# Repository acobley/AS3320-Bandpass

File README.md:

View this project on [CADLAB.io](https://cadlab.io/project/24867). 

# AS3320-Bandpass
This is a bandpass filter with CV control of the resonce based on a single  AS3320

Status: In Design

Board: No Board sent to manfacturer.

## Licence and attribution
CC4.0

Based on the work by forestcaver/Analog-Voice (github)

## Major aditions
* Added CV on Resonance
* Moved to larger components (0804)
* Added more inputs and input mixer out.

## History
as3320-BandPass-Dev2 10/Nov/2021 This board is untested. D6 repositioned.

as3320-BandPass-Dev1  2/oct/2021 D6 is shorted to FM level POT Do NOT USE (To use, a TTH D6 can be substituted  betweenthe output pin and ground.

10/Nov/2021 Rec2021 Recieved and will be built with above botch. 

as3320-BandPass Layout version

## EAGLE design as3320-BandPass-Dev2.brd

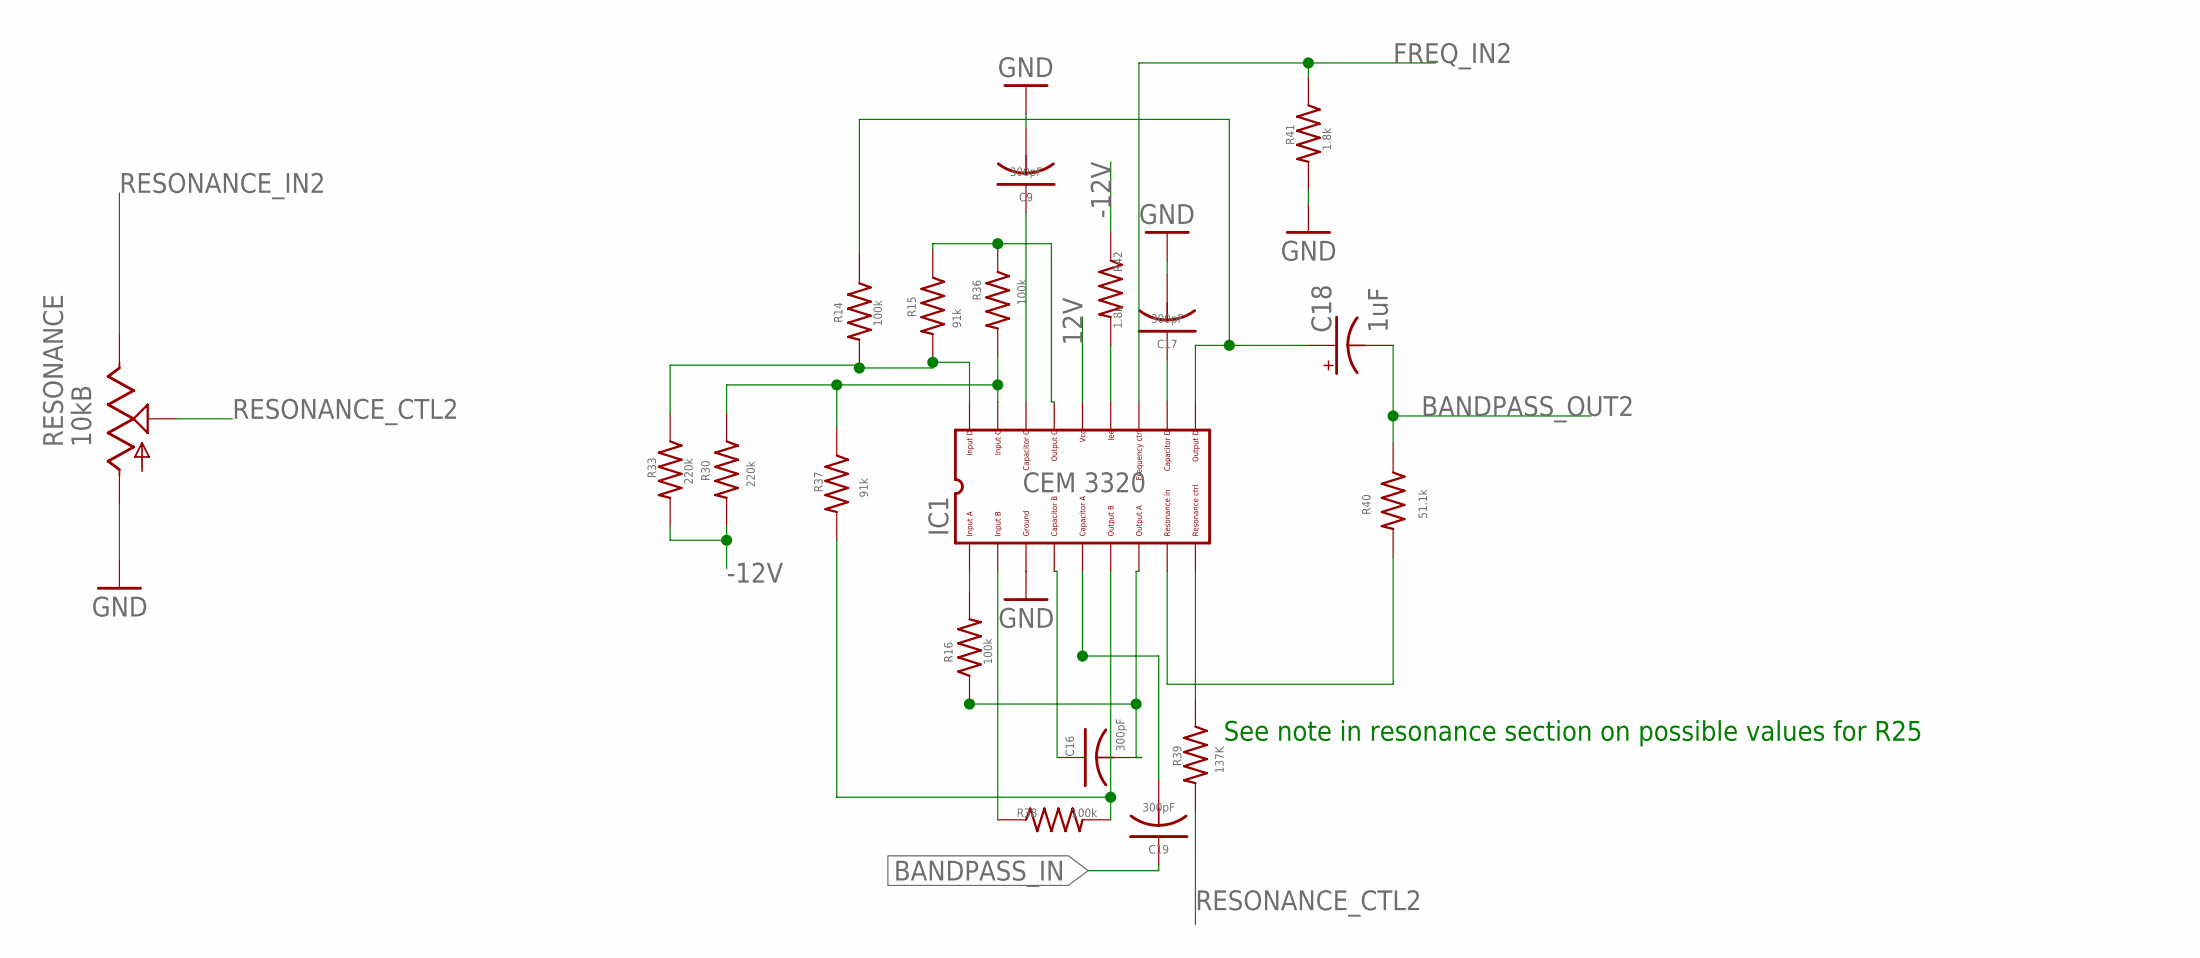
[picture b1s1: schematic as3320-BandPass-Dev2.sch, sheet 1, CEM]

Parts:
C9, C16, C17, C19: 300pF; C0805K
C18: 1uF; PANASONIC_B
IC1: CEM3320; DIL18
R14, R16, R36, R38: 100k; GMSN_M0805
R15, R37: 91k; GMSN_M0805
R30, R33: 220k; GMSN_M0805
R39: 137K; GMSN_M0805
R40: 51.1k; GMSN_M0805
R41, R42: 1.8k; GMSN_M0805
RESONANCE: 10kB; ALPS_POT_VERTICAL

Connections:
12V: IC1.14; also elsewhere on the board
-12V: R30.2, R33.2, R42.1; also elsewhere on the board
BANDPASS_IN: C19.1; also elsewhere on the board
BANDPASS_OUT2: C18.-, R40.1; also elsewhere on the board
FREQ_IN2: IC1.12, R41.1; also elsewhere on the board
GND: C9.2, C17.2, IC1.3, R41.2, RESONANCE.P$3 (A); also elsewhere on the board
unnamed: C17.1, IC1.11
unnamed: IC1.9, R39.1
unnamed: IC1.8, R40.2
unnamed: IC1.13, R42.2
unnamed: C9.1, IC1.16
unnamed: C18.+, IC1.10, R14.1
unnamed: C19.2, IC1.5
unnamed: C16.2, IC1.7, R16.1
unnamed: C16.1, IC1.4
unnamed: IC1.2, R38.1
unnamed: IC1.6, R37.2, R38.2
unnamed: IC1.1, R16.2
unnamed: IC1.17, R30.1, R36.2, R37.1
unnamed: IC1.15, R15.1, R36.1
unnamed: IC1.18, R14.2, R15.2, R33.1
RESONANCE_CTL2: R39.2, RESONANCE.P$2 (S)
RESONANCE_IN2: RESONANCE.P$1 (E); also elsewhere on the board

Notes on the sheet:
See note in resonance section on possible values for R25

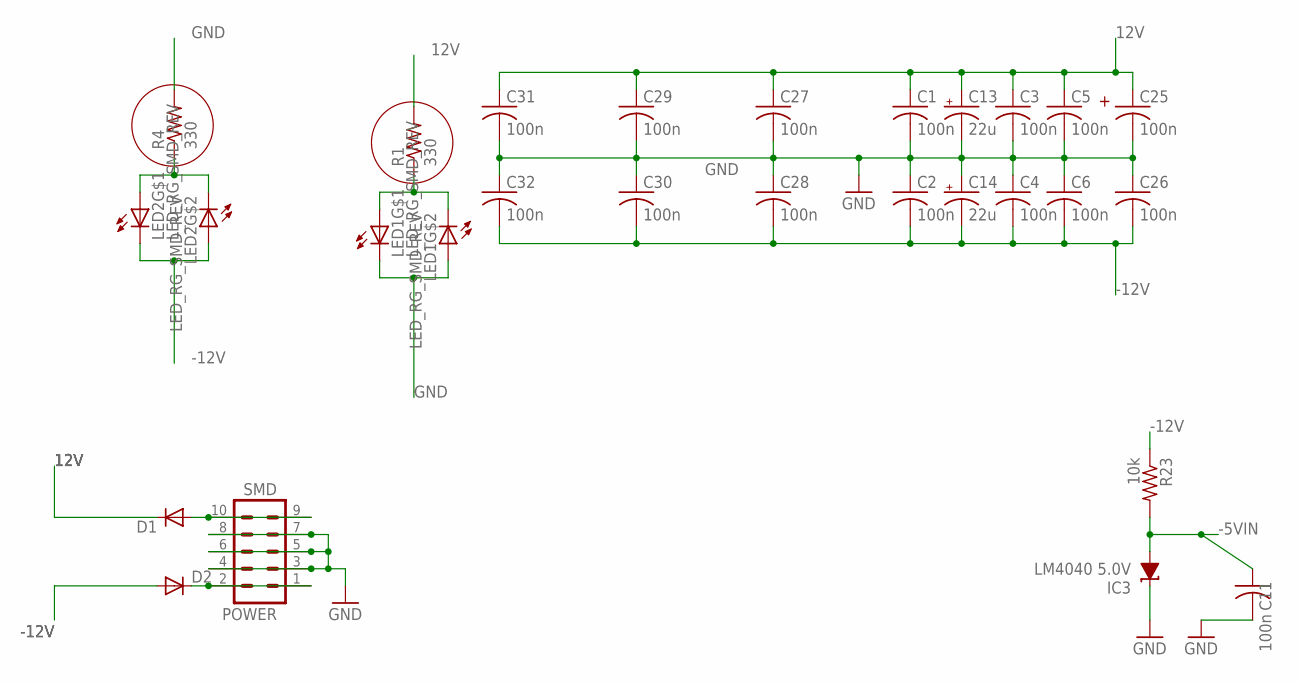
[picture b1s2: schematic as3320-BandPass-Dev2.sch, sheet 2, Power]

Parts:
C1, C2, C3, C4, C5, C6, C25, C26, C27, C28, C29, C30, C31, C32: 100n; C0805K
C11: 100n; GMSN_C0805K
C13, C14: 22u; PANASONIC_B
D1, D2: 1N5819HW; SOD123
IC3: LM4040 5.0V; DBZ_R-PDSO-G3
LED1, LED2: LED_RG_SMD_REV; LSG_T77K
POWER: SMD; 2X5-SHROUDED_SMD
R1, R4: 330; GMSN_M0805
R23: 10k; GMSN_M0805

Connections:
12V: C1.1, C3.1, C5.1, C13.+, C25.1, C27.1, C29.1, C31.1, D1.C, R1.2; also elsewhere on the board
-5VIN: C11.1, IC3.2 (A), R23.2; also elsewhere on the board
-12V: C2.2, C4.2, C6.2, C14.-, C26.2, C28.2, C30.2, C32.2, D2.A, LED2.1 (C), LED2.4 (A), R23.1; also elsewhere on the board
-12V-P: D2.C, POWER.1, POWER.2
GND: C1.2, C2.1, C3.2, C4.1, C5.2, C6.1, C11.2, C13.-, C14.+, C25.2, C26.1, C27.2, C28.1, C29.2, C30.1, C31.2, C32.1, IC3.1 (C), LED1.1 (C), LED1.4 (A), POWER.3, POWER.4, POWER.5, POWER.6, POWER.7, POWER.8, R4.2; also elsewhere on the board
unnamed: D1.A, POWER.9, POWER.10
unnamed: LED2.2 (A), LED2.3 (C), R4.1
unnamed: LED1.2 (A), LED1.3 (C), R1.1

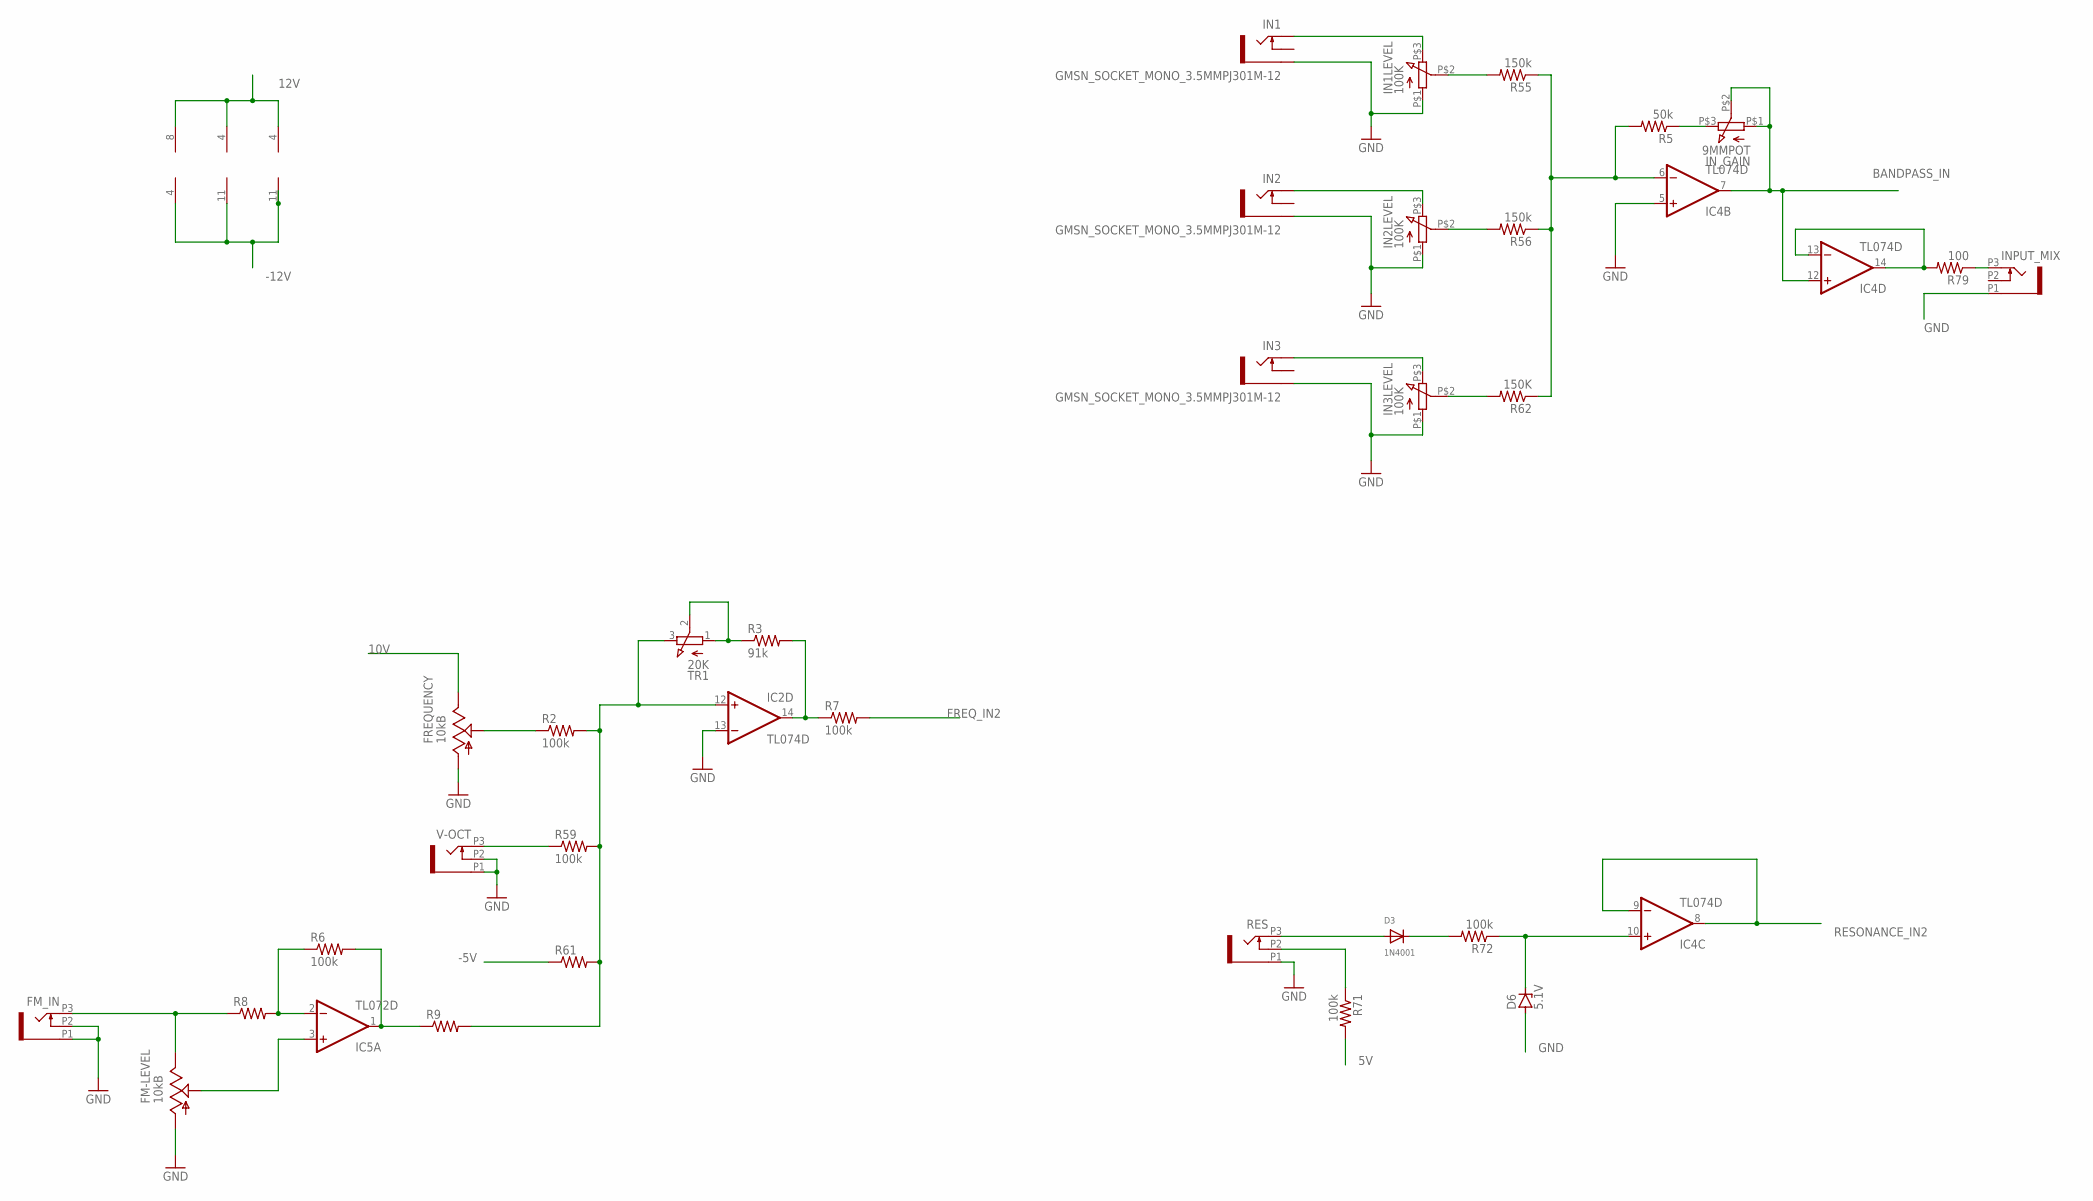
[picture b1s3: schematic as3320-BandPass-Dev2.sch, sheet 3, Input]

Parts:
D3: 1N4001; SMADIODE
D6: 5.1V; SOT23
FM-LEVEL: 10kB; ALPS_POT_VERTICAL
FM_IN: PJ301_THONKICONN6; WQP_PJ_301M6
FREQUENCY: 10kB; ALPS_POT_VERTICAL
IC2, IC4: TL074D; SO14
IC5: TL072D; SO08
IN1, IN2, IN3: GMSN_SOCKET_MONO_3.5MMPJ301M-12; GMSN_PJ301M-12
IN1LEVEL, IN2LEVEL, IN3LEVEL: 100K; POT
INPUT_MIX: PJ301_THONKICONN6; WQP_PJ_301M6
IN_GAIN: 9MMPOT; POT
R2, R6, R7, R59, R72: 100k; GMSN_M0805
R3: 91k; GMSN_M0805
R5: 50k; GMSN_M0805
R8, R9, R61: 62k; GMSN_M0805
R55, R56: 150k; R0805
R62: 150K; R0805
R71: 100k; R0805
R79: 100; GMSN_M0805
RES: PJ301_THONKICONN6; WQP_PJ_301M6
TR1: 20K; TRIMMER_TH3
V-OCT: PJ301_THONKICONN6; WQP_PJ_301M6

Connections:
5V: R71.2; also elsewhere on the board
10V: FREQUENCY.P$1 (E); also elsewhere on the board
12V: IC2.4 (V+), IC4.4 (V+), IC5.8 (V+); also elsewhere on the board
-5V: R61.1; also elsewhere on the board
-12V: IC2.11 (V-), IC4.11 (V-), IC5.4 (V-); also elsewhere on the board
BANDPASS_IN: IC4.7 (OUT), IC4.12 (+IN), IN_GAIN.P$1 (1), IN_GAIN.P$2 (2); also elsewhere on the board
FREQ_IN2: R7.2; also elsewhere on the board
GND: D6.1 (A), FM-LEVEL.P$3 (A), FM_IN.P1 (1), FM_IN.P2 (2), FREQUENCY.P$3 (A), IC2.13 (-IN), IC4.5 (+IN), IN1.GND (SLEEVE), IN1LEVEL.P$1 (1), IN2.GND (SLEEVE), IN2LEVEL.P$1 (1), IN3.GND (SLEEVE), IN3LEVEL.P$1 (1), INPUT_MIX.P1 (1), RES.P1 (1), V-OCT.P1 (1), V-OCT.P2 (2); also elsewhere on the board
unnamed: IC5.2 (-IN), R6.1, R8.2
unnamed: IC2.14 (OUT), R3.2, R7.1
unnamed: IC5.1 (OUT), R6.2, R9.1
unnamed: FREQUENCY.P$2 (S), R2.1
unnamed: FM-LEVEL.P$2 (S), IC5.3 (+IN)
unnamed: FM-LEVEL.P$1 (E), FM_IN.P3 (3), R8.1
unnamed: R71.1, RES.P2 (2)
unnamed: IC2.12 (+IN), R2.2, R9.2, R59.2, R61.2, TR1.3
unnamed: IN_GAIN.P$3 (3), R5.1
unnamed: R59.1, V-OCT.P3 (3)
unnamed: R3.1, TR1.1, TR1.2
unnamed: IN1.TIP, IN1LEVEL.P$3 (3)
unnamed: IN2.TIP, IN2LEVEL.P$3 (3)
unnamed: D3.A, RES.P3 (3)
unnamed: IN1LEVEL.P$2 (2), R55.2
unnamed: IN2LEVEL.P$2 (2), R56.2
unnamed: IN3.TIP, IN3LEVEL.P$3 (3)
unnamed: IN3LEVEL.P$2 (2), R62.2
unnamed: IC4.6 (-IN), R5.2, R55.1, R56.1, R62.1
unnamed: D3.C, R72.2
unnamed: D6.3 (C), IC4.10 (+IN), R72.1
unnamed: IC4.13 (-IN), IC4.14 (OUT), R79.2
unnamed: INPUT_MIX.P3 (3), R79.1
RESONANCE_IN2: IC4.8 (OUT), IC4.9 (-IN); also elsewhere on the board

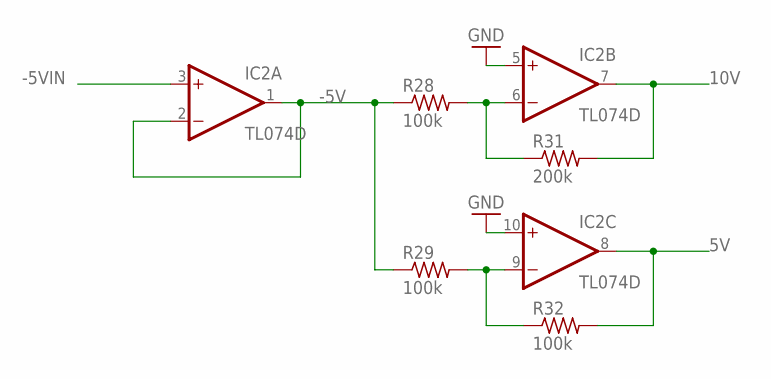
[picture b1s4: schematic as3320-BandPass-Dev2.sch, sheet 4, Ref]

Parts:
IC2: TL074D; SO14
R28, R29, R32: 100k; GMSN_M0805
R31: 200k; GMSN_M0805

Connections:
5V: IC2.8 (OUT), R32.2; also elsewhere on the board
10V: IC2.7 (OUT), R31.2; also elsewhere on the board
-5V: IC2.1 (OUT), IC2.2 (-IN), R28.1, R29.1; also elsewhere on the board
-5VIN: IC2.3 (+IN); also elsewhere on the board
GND: IC2.5 (+IN), IC2.10 (+IN); also elsewhere on the board
unnamed: IC2.9 (-IN), R29.2, R32.1
unnamed: IC2.6 (-IN), R28.2, R31.1

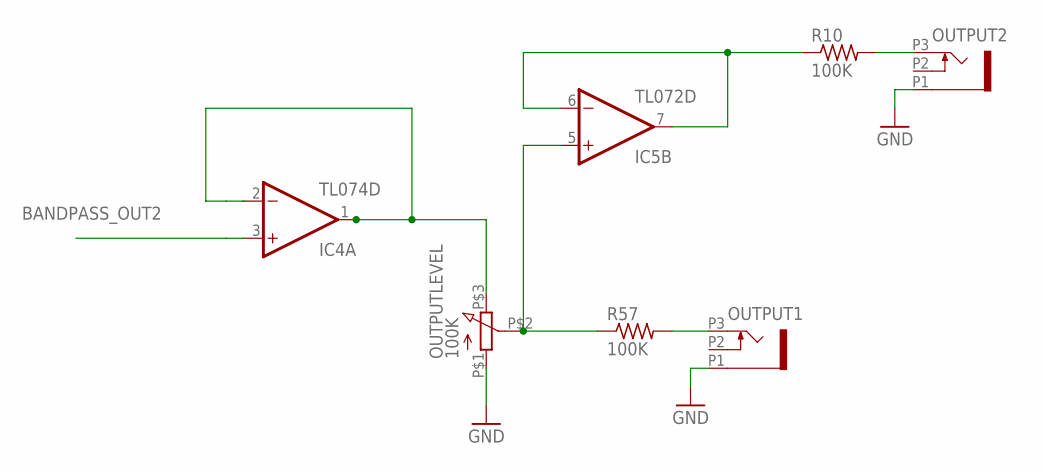
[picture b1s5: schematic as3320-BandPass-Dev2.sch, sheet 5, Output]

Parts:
IC4: TL074D; SO14
IC5: TL072D; SO08
OUTPUT1, OUTPUT2: PJ301_THONKICONN6; WQP_PJ_301M6
OUTPUTLEVEL: 100K; POT
R10, R57: 100K; GMSN_M0805

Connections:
BANDPASS_OUT2: IC4.3 (+IN); also elsewhere on the board
GND: OUTPUT1.P1 (1), OUTPUT2.P1 (1), OUTPUTLEVEL.P$1 (1); also elsewhere on the board
unnamed: IC5.5 (+IN), OUTPUTLEVEL.P$2 (2), R57.1
unnamed: IC5.6 (-IN), IC5.7 (OUT), R10.1
unnamed: IC4.1 (OUT), IC4.2 (-IN), OUTPUTLEVEL.P$3 (3)
O1: OUTPUT2.P3 (3), R10.2
O2: OUTPUT1.P3 (3), R57.2

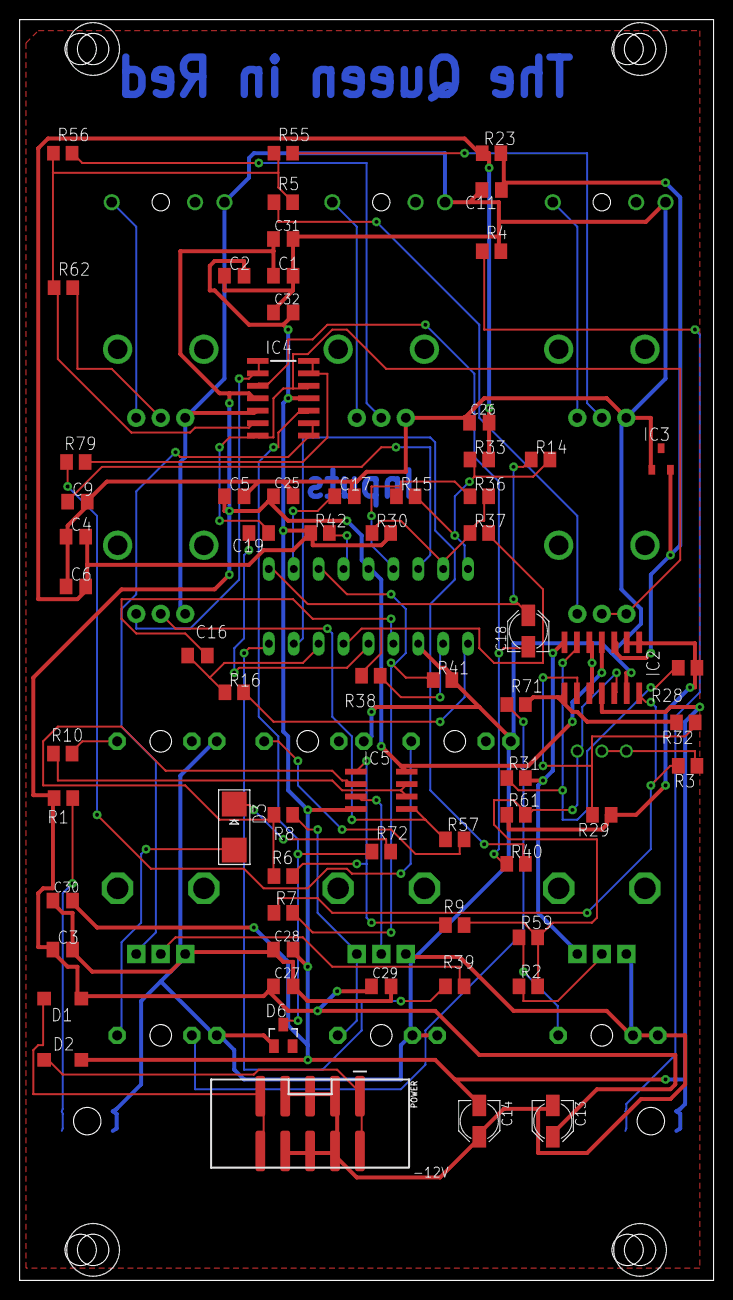
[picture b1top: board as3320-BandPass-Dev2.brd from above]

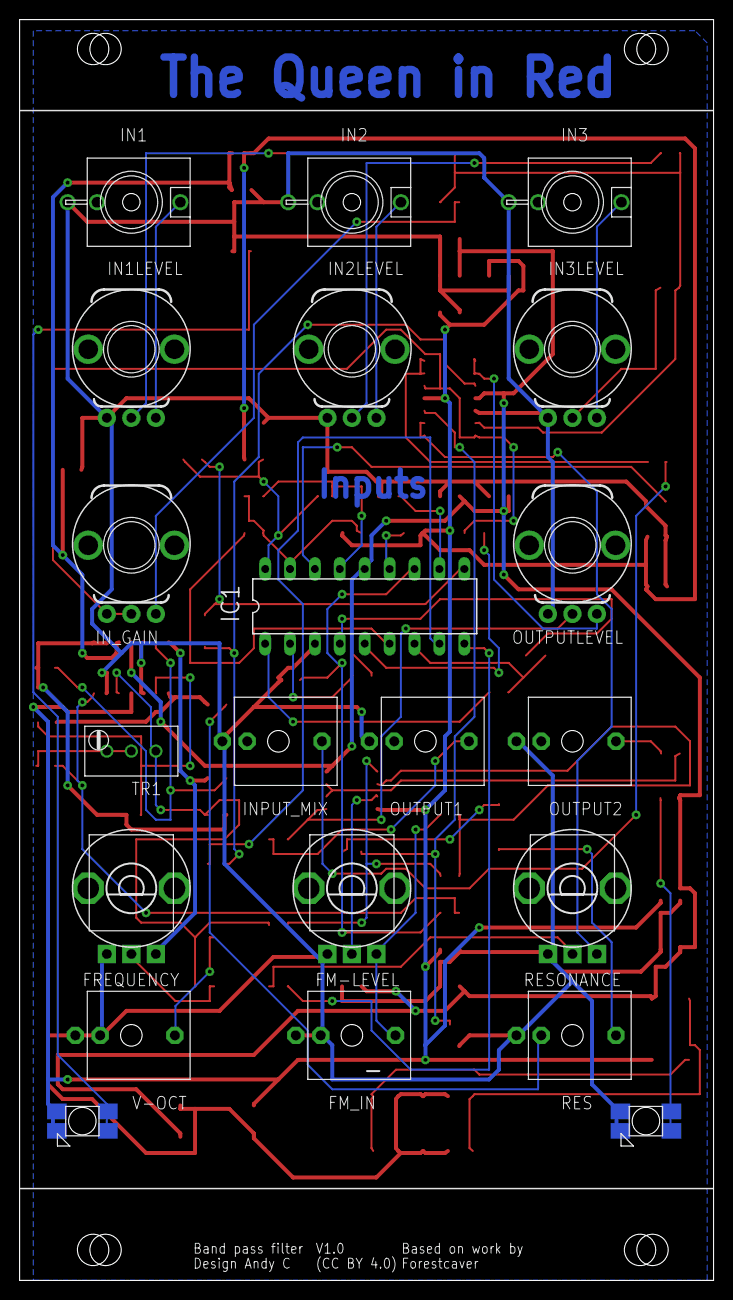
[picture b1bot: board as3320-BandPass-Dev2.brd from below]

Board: 2 copper layers, 70.8 x 128.6 mm, 92 parts (21 on the bottom side), 61 nets.

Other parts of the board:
U$2, U$3, U$4, U$5: MOUNTING_HOLE

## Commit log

2021-09-09 added Board and Schematic
2021-09-09 Updated to include FM in
2021-09-09 added power for IC5
2021-10-21 De1 in evaluation
2021-10-23 Added 2nd output
2021-10-23 Backlink to CADLAB.io has been added.
2021-10-23 Routed
2021-10-23 Added png of panel design
2021-11-10 Dev 2 board added

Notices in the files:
as3320-BandPass-Dev2.brd:
(CC BY 4.0)
parts and their libraries:
SparkFun-Connectors: Licensing: Creative Commons ShareAlike 4.0 International - https://creativecommons.org/licenses/by-sa/4.0
